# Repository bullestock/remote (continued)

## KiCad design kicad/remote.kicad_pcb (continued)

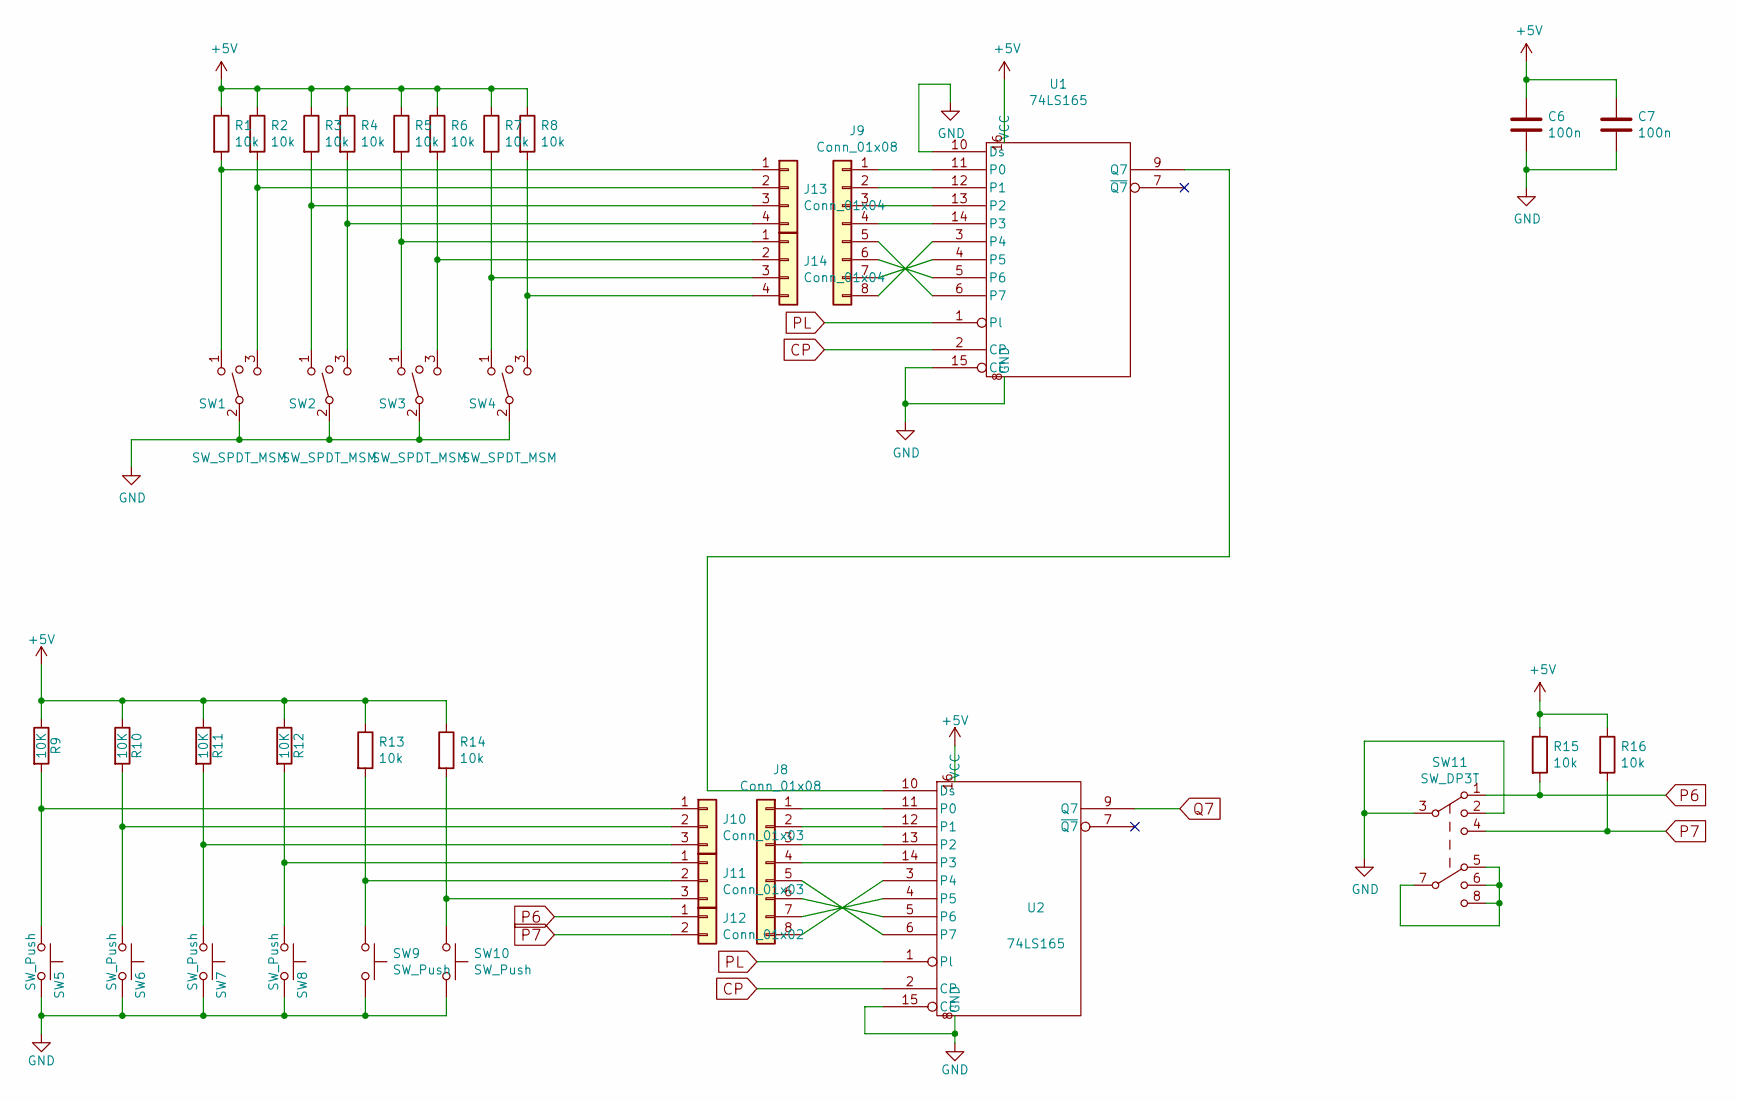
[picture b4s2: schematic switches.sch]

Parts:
C6, C7: 100n; C_0805_2012Metric
J8, J9: Conn_01x08; JST_XH_B08B-XH-A_1x08_P2.50mm_Vertical
J10, J11: Conn_01x03; JST_XH_B03B-XH-A_1x03_P2.50mm_Vertical_Milling
J12: Conn_01x02; JST_XH_B02B-XH-A_1x02_P2.50mm_Vertical_Milling
J13, J14: Conn_01x04; JST_XH_B04B-XH-A_1x04_P2.50mm_Vertical_Milling
R1, R2, R3, R4, R5, R6, R7, R8, R13, R14, R15, R16: 10k; R_0805_2012Metric
R9, R10, R11, R12: 10K; R_0805_2012Metric
SW1, SW2, SW3, SW4: SW_SPDT_MSM; Switch_1x03_P5.08mm
SW5, SW6, SW7, SW8, SW9, SW10: SW_Push; Switch_1x02_P6mm
SW11: SW_DP3T; Switch_2x03_P3mm_Slide
U1, U2: 74LS165; DIP-16_W7.62mm

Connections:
+5V: C6.1, C7.1, R1.1, R2.1, R3.1, R4.1, R5.1, R6.1, R7.1, R8.1, R9.1, R10.1, R11.1, R12.1, R13.1, R14.1, R15.1, R16.1, U1.16 (VCC), U2.16 (VCC); also elsewhere on the board
CP: U1.2 (CP), U2.2 (CP); also elsewhere on the board
GND: C6.2, C7.2, SW1.2, SW2.2, SW3.2, SW4.2, SW5.2, SW6.2, SW7.2, SW8.2, SW9.2, SW10.2, SW11.2, SW11.3, U1.8 (GND), U1.10 (Ds), U1.15 (CE), U2.8 (GND), U2.15 (CE); also elsewhere on the board
unnamed: J8.1, U2.11 (P0)
unnamed: J8.2, U2.12 (P1)
unnamed: J8.3, U2.13 (P2)
unnamed: J8.4, U2.14 (P3)
unnamed: J8.5, U2.6 (P7)
unnamed: J8.6, U2.5 (P6)
unnamed: J8.7, U2.4 (P5)
unnamed: J8.8, U2.3 (P4)
unnamed: J9.1, U1.11 (P0)
unnamed: J9.2, U1.12 (P1)
unnamed: J9.3, U1.13 (P2)
unnamed: J9.4, U1.14 (P3)
unnamed: J9.5, U1.6 (P7)
unnamed: J9.6, U1.5 (P6)
unnamed: J9.7, U1.4 (P5)
unnamed: J9.8, U1.3 (P4)
unnamed: J10.1, R9.2, SW5.1
unnamed: J10.2, R10.2, SW6.1
unnamed: J10.3, R11.2, SW7.1
unnamed: J11.1, R12.2, SW8.1
unnamed: J11.2, R13.2, SW9.1
unnamed: J11.3, R14.2, SW10.1
unnamed: J13.1, R1.2, SW1.1
unnamed: J13.2, R2.2, SW1.3
unnamed: J13.3, R3.2, SW2.1
unnamed: J13.4, R4.2, SW2.3
unnamed: J14.1, R5.2, SW3.1
unnamed: J14.2, R6.2, SW3.3
unnamed: J14.3, R7.2, SW4.1
unnamed: J14.4, R8.2, SW4.3
unnamed: SW11.5, SW11.6, SW11.7, SW11.8
unnamed: U1.9 (Q7), U2.10 (Ds)
P6: J12.1, R15.2, SW11.1
P7: J12.2, R16.2, SW11.4
PL: U1.1 (Pl), U2.1 (Pl); also elsewhere on the board
Q7: U2.9 (Q7); also elsewhere on the board

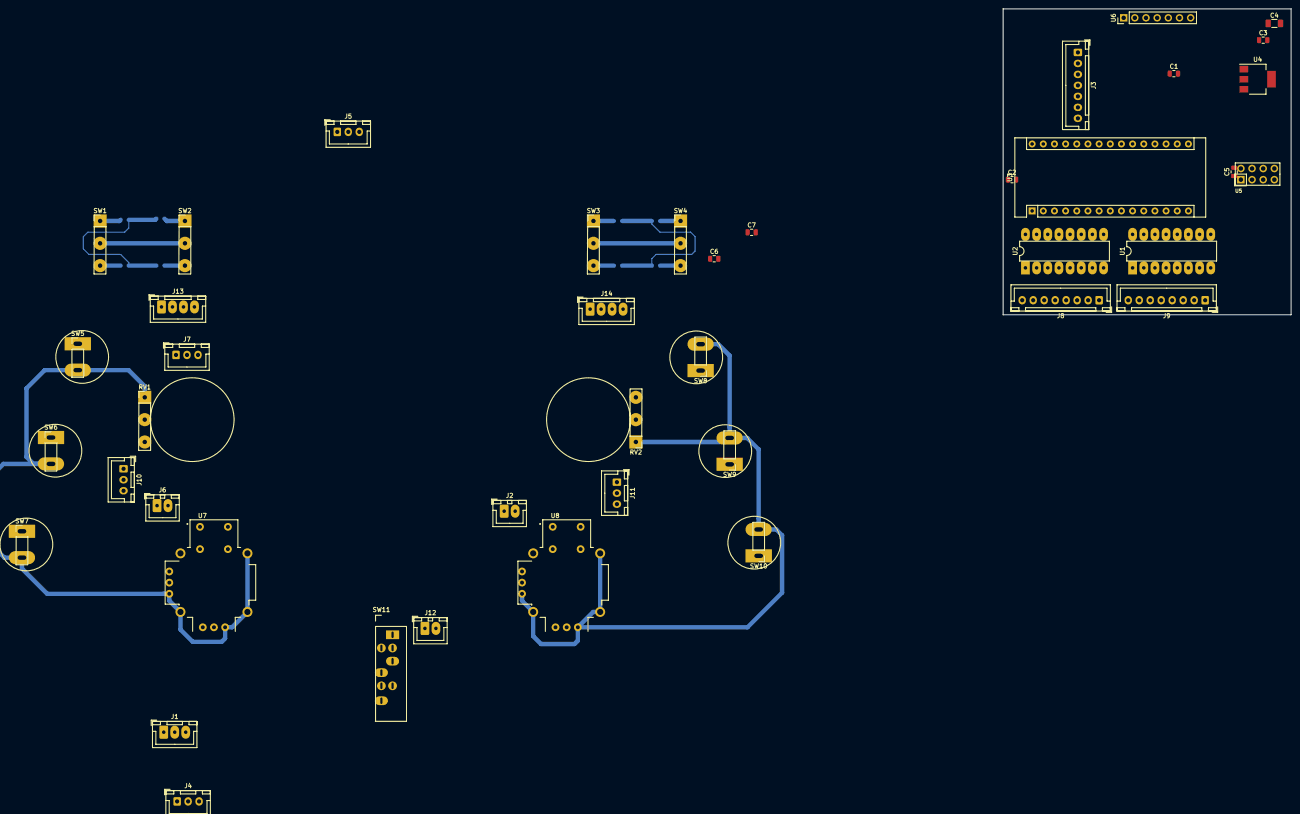
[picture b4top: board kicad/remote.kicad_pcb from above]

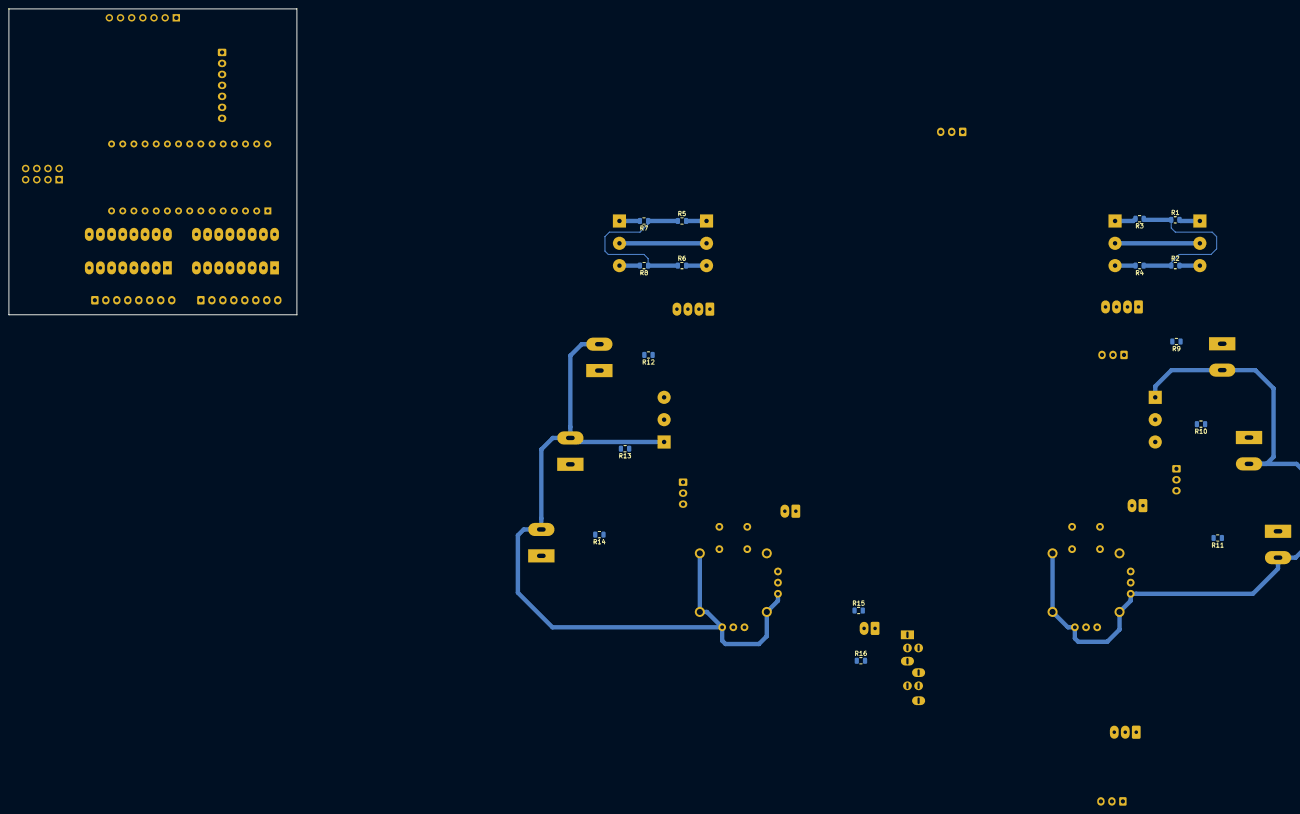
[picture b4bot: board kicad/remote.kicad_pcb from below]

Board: 2 copper layers, 65.5 x 69.6 mm, 62 parts (16 on the bottom side), 64 nets.

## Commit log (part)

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2017-07-13 Diagram.
2017-07-14 Display test.
2017-08-05 Ping works.
2017-08-09 Send joystick data.
2017-08-09 Add RF24 lib.
2017-08-09 Air frame format.
2017-08-09 Update diagram.
2017-08-09 Show round trip delay nicely.
2017-08-12 Read switches.
2017-08-12 Fix pin numbering.
2017-08-12 Add switches field.
2017-08-12 Fix pin use.
2017-08-16 Read potentiometers.
2017-08-18 Add joystick cover.
2017-08-19 Do not set .switches to 0.
2017-08-21 Set power level to max. Adjust node addresses. Clean up statistics display.
2017-09-20 Enlarge hole.
2017-09-20 Add battery voltage to protocol.
2017-09-30 Make higher.
2017-09-30 Add CRC to protocol.
2017-10-01 Show number of CRC errors.
2017-10-01 Blink on connection loss.
2020-01-25 Prepare for PCB.
2020-01-26 Add more switches, footprints.
2020-01-26 Place switches, etc. Split up into two boards.
2020-01-27 Work on layout.
2020-01-31 Split into two projects.
2020-01-31 Update for I2C display.
2020-01-31 Update to 4-pin I2C display.
2020-02-01 Fix joystick footprint.
2020-02-01 Fix toggle footprints.
2020-02-01 Update slide switch footprint.
2020-02-01 Update holes in switch footprints.
2020-02-01 Move jumper.
2020-02-02 First feeble beginnings.
2020-02-02 Add slide switch depression.
2020-02-03 Make top rounded.
2020-02-03 Hollow it out.
2020-02-03 Fix slide cutout.
2020-02-04 Move outline data to separate file.
2020-02-04 Center around origo.
2020-02-04 Convert to module.
2020-02-04 Add joystick covers.
2020-02-04 Add joystick depressions.
2020-02-07 Reduce height.
2020-02-07 Make slide switch cover separate.
2020-02-07 Fix thickness.
2020-02-07 Make joystick cover a separate piece; add PCB standoffs.
2020-02-08 Fix dimensions.
2020-02-08 Reduce flange a bit.
2020-02-08 Fix slide position.
2020-02-08 Adjust pot holes.
2020-02-08 Make PCB supports thicker.
2020-02-08 Offset holes.
2020-02-08 Move PCB mounts along with holes.
2020-02-09 Add screw studs.
2020-02-09 Fix upper screw studs.
2020-02-09 Fix right screw stud.
2020-02-14 Fix slide cutout position.
2020-02-14 Reduce flange diameter.
2020-02-14 Create basic bottom shape.
2020-02-15 Add PCB supports and studs.
2020-02-20 Add charger hole etc.
2020-02-20 Add tabs for fixing charger.
2020-02-21 Adjust slide switch position.
2020-02-21 Allow a bit more room above the joystick.
2020-02-21 Mess around.
2020-02-21 Add defs.
2020-02-21 Adapt for new-style joystick/switch.
2020-02-21 Add cutout for bezel.
2020-02-21 Simplify.
2020-02-21 Add new stuff.
2020-02-22 Make slide hole wider.
2020-02-29 Move display back to center.
2020-02-29 Add antenna hole.
2020-02-29 Add controller screw studs, determine overall height.
2020-02-29 Change LiPo to 500 mAh.
2020-02-29 Add slope.
2020-02-29 Increase thickness.
2020-02-29 Add tab for antenna hole.
2020-03-01 Add insert holes to mainboard studs.
2020-03-01 Fix bug.
2020-03-01 Fix joystick and slide positions.
2020-03-01 Make screwstud() independt of th, add insert hole.
2020-03-01 Make pcbsupport() independt of th.
2020-03-01 Make PCB supports conical, increase height.
2020-03-01 Increase thickness, fix display and antenna holes.
2020-03-01 Fix joystick studs bug.
2020-03-01 Remove pins for joystickcovers and slide cover.
2020-03-03 Fix tab position.
2020-03-03 Fix controller studs.
2020-03-03 Fix antenna hole.
2020-03-03 Increase lipo length.
2020-03-03 Make charger hole oval.
2020-03-03 Make PCB supports stronger.
2020-03-03 Lower antenna.
2020-03-03 Make screw studs conical.
2020-03-03 Make recessed studs conical.
2020-03-03 Add one more PCB support.
2020-03-06 Fix stuff.
2020-03-22 Update for new controller board, and SH1106 display.
2020-03-23 Make a local copy of SH1106 driver.
2020-03-23 Backup.
2020-03-23 Remove SPI support.
2020-03-23 Divide display into 2 pages.
2020-03-26 Fix reading of switches.
2020-03-26 Use all bits for switches.
2020-07-17 Update for Arch.
2020-07-17 Bump magic value.
2020-07-17 Split switches into separate member vars.
2020-07-17 Enlarge stud holes a bit.
2020-07-17 Use joystick_dep_h.
2020-07-17 Adjust dimensions.
2020-07-17 Remove holes.
2020-07-17 Update schematic.
2020-07-17 Add mode control.
2020-09-12 Make radio work.
2023-05-18 Start migration to ESP32.
2023-05-20 Add debug connector.
2023-05-25 Work on routing.
2023-05-28 Complete routing.
2023-06-29 Fix capacitor values.
2024-04-09 Add switches, regulator, etc.
2024-04-09 Move nRF footprint.
2024-04-09 Finish routing.
2024-04-13 Add nRF mounting screw.
2024-05-02 Update KiCAD version.
2024-05-05 Init HW.
2024-05-05 Implement ADC read.
2024-05-06 Possibly fix ADC read.
2024-05-08 Add test point.
2024-05-08 Add read_switches().
2024-05-08 Initialize radio.
2024-05-09 Use mirf as a submodule.
2024-05-09 Add display driver.
2024-05-09 Add SSD1306 component.
2024-05-10 Spacer for display header.
2024-05-12 Start integrating radio.
2024-05-18 Add I2C scan command.
2024-05-18 Fix display initialization.
2024-05-20 Fix read_adc() return value.
2024-05-20 Fix display offset.
2024-05-20 Implement radio test command.
2024-05-21 Add lasercut front.
2024-05-27 Add split mainboard PCB.
2024-05-28 Add more power.
2024-05-28 Rename project.
2024-06-03 Place switches on millimeter grid.
2024-06-03 Improve outline.
2024-06-06 Fix JST 3D models.
2024-06-06 Fix more models.
2024-06-06 Add fills.
2024-06-08 Enlarge stick lock holes.
2024-06-08 Order PCB.
2024-07-13 Fix read of switches.
2024-07-13 Add support for reading all ADC channels.
2024-07-13 Reduce warnings.
2024-07-13 Update for esp-idf 5.2.2.
2024-07-13 Update for new PCB.
2024-07-14 First attempt.
2024-07-14 Carve out interior.
2024-07-14 Add controller standoffs.
2024-07-14 Add mainboard standoffs.
2024-07-15 Split into subdirs.
2024-07-16 Adjust PCB positions, add antenna cutouts.
2024-07-16 Import outline again.
2024-07-16 Add charging port.
2024-07-22 Fix mainboard standoff positions.
2024-07-22 Add screwposts.
2024-07-27 Make room for lid screwposts.
2024-07-31 Adjust.
2024-08-10 Use magnet instead of screw.
2024-08-10 Adjust height.
2024-08-10 Adjust display hole.
2024-08-10 Move common stuff to defs.h.
2024-08-10 Refactor.
2024-08-10 Basic form.
2024-08-10 Fix screwposts, add pushbutton holes.
2024-08-10 Add toggle switch holes.
2024-08-10 Add pot, joystick holes.
2024-08-10 Add joystick screw holes.
2024-08-10 Add remaining holes.
2024-08-11 Mount for charger module.
2024-08-11 Mount for SMPS module.
2024-08-11 Box for 700 mAh LiPo battery.
2024-08-12 Lid for battery box.
2024-08-12 Increase insert hole diameter.
2024-08-12 Raise mainboards.
2024-08-12 Update.
2024-09-01 Place upright.
2024-09-01 Remove stray fills.
2024-09-01 Add live view.
2024-09-01 Add readout of slide switch.
2024-09-01 Put ADC Vref onto analog connector.
2024-09-02 Fix analog channel assignments.
2024-09-02 Implement stick calibration.
2024-09-02 Clamp stick values.
2024-09-03 Tweak battery measurement.
2024-09-08 Fix radio handling.
2024-09-08 Fix memcpy.
2024-09-08 Implement useful display.
2024-09-08 Cleanup.
2024-09-08 Bump.
2024-10-25 Adjust fillet.
2024-10-27 Initial ESPNOW PoC.
2024-10-27 Use correct frame structure.
2024-10-27 Send data properly.
2024-10-27 Complete conversion to ESPNOW.
2024-11-01 Store other MAC in NVS.
2024-11-03 Remove nRF24L01.
2024-11-03 Power directly from battery.
2024-11-03 Add large decoupling cap.
2024-11-03 Make mounting R1/R2 optional.
2024-11-03 Fix missing trace.
2024-11-16 Fix bad format specifier.
2024-11-16 Fix swapped toggles.
2024-11-16 Change toggles field to uint8.
2024-11-16 Fix switched up/down for right side toggles.
2024-11-16 Add stick filtering.
2024-11-16 Add support for setting LP rate in NVS.
2024-12-09 Increase height.
2024-12-09 Use Vref for pots and sticks.
2024-12-13 Mount antenna in case wall.
2024-12-13 Move charging port to right side.
2024-12-16 Some charger modules are wider than others.
2025-01-03 Update display in separate thread.
2025-01-04 Check if display is present. Add sanity check for ADC values.
2025-01-07 Preload filter to improve zeroing.
2025-01-07 Cosmetic fixes.
2025-02-28 Try to fix submodule.
2025-02-28 Fix POT2 config.
2025-03-14 Fix debug output.
2025-03-16 No changes.
2025-04-19 Add support for showing stick calibration.
2025-04-19 Sticks now send (-1, 1), pots send (0, 1).
2025-04-19 Fix pot values.
2025-12-30 Update for ESP-IDF 5.5.
2025-12-30 Change display from SSD1306 to SH1107.
2025-12-30 Add X offset.
2025-12-30 Hack: make clear work properly.
2025-12-30 Remove old display driver component.
2025-12-30 Update protocol.
2025-12-31 Fix display test.
2025-12-31 Reduce display flicker.
2025-12-31 Bezel for 128 x 128 display.
2026-01-02 Move power mapping to remote.
2026-01-02 Cosmetics.
2026-05-24 Update for ESP-IDF 6.0.
2026-05-25 Update to protocol version 4.
2026-05-31 Implement sound handling (browse still missing).
2026-06-01 Split effects and music.
